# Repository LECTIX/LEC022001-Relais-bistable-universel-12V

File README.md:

# LEC022001 - Relais bistable universel 12V
Fichiers sources pour le produit LEC022001

## Description du produit

Ce module est un relais bistable disposant de toutes les protections nécessaires pour être utilisé avec une tension de 12 à 16 V alternative ou continue.
Comme tous les relais bistable, une seule impulsion est nécessaire pour faire basculer les contacts inverseurs d'un côté ou de l'autre, ce qui le rend idéal pour être utilisé avec des ILS ou bien des boutons poussoirs.
- **ALIMENTATION** 12 – 16 V AC / DC.
- **2 CONTACTS INVERSEURS** indépendants (DPDT).
- **FAIBLE CONSOMMATION** de 15 mA lorsqu'une des bobines relais est alimentée.
- **POUVOIR DE COUPURE** de 2A.

## Applications

- Cantonnement analogique
- Zone de protection faller car system
- Boucle de retournement
- Extension de contact inverseurs (aiguillages, relais, interrupteurs, …)
- Gestion d'un passage à niveau

## Installation

L’installation est simple et rapide :

1. Brancher le commun au pole négatif de l'alimentation.
1. Pour chacune des bornes R et S, intercaller un interrupteur ou équivalent (ILS, pédale, capteur Hall, contact inverseur, …) entre la borne et le pole positif de l'alimentation.
1. Les contacts inverseurs du relais réagissent en fonction du bouton sur lequel on appui.

**Attention** : Il ne faut en aucun cas alimenter les 2 bornes R et S simultanément.

## Utiliser les fichiers sources pour fabriquer le produit

Il n'est **pas nécessaire de savoir souder ou d'être bon en électronique** pour se procurer ce produit. Grâce aux fichiers sources publiés ici, vous pouvez être en mesure de faire fabriquer ce produit par un sous traitant.

### Faire fabriquer chez un sous traitant

Il est aujourd'hui possible de faire fabriquer à moindre cout des cartes électroniques. Nous recommendons [JLCPCB](https://jlcpcb.com/) si vous voulez aller au moins cher. Si vous préférez un acteur européen, [eurocircuits](https://www.eurocircuits.com/) est un des acteurs reconnus.

1. Télécherger les sources de ce produit en cliquant sur le bouton `Code`, puis `Download ZIP`.
1. Décompresser le dossier.
1. Les fichiers pour la fabrication se trouvent dans le répertoire `hardware/prod`.
1. Se connecter sur [https://cart.jlcpcb.com/quote](https://cart.jlcpcb.com/quote)
1. Cliquer sur le bouton `Add gerber file` et sélectionner le fichier `gerbers.zip`.
1. Sélectionnez la quantité de cartes que vous souhaitez dans le champs `PCB Qty`.
1. Laisser toutes les autres options par défaut, puis cliquez sur le toggle switch en face de `PCB Assembly`, et enfin sur le bouton `confirm`.
1. Une preview de la carte électronique sans les composants doit apparaitre. Cliquez sur `NEXT`.
1. Cliquez sur le bouton `Add BOM File`, puis sélectionnez le fichier `bom.csv`
1. Cliquez sur le bouton `Add CPL File`, puis sélectionnez le fichier `pos.csv`
1. **Vérifier que tous les composants sont en stock** et bien sélectionnés, puis cliquez sur `NEXT`.
1. Une preview de la carte avec ses composants apparait. Continuer le chemin en cliquant sur `NEXT`.
1. Le prix final apparait. Sélectionnez la catégorie du produit, puis cliquez sur `SAVE TO CART`.
1. Une fois sauvegardé dans votre panier, vous pouvez valider votre commande et choisir le moyen d'acheminement. Afin de ne pas avoir à se préoccuper des frais de douane, nous vous conseillons de choisir une méthode d'expédition DDP.

Vous receverez vos cartes sous 1 à 3 semaines. 

**Nous ne sommes en aucun cas responsables des cartes qui arriveraient défectueuses ou non fonctionnelles.**

### Modifications des fichiers sources

Installez kicad 6 (ou version supérieure), et ouvrez le fichier LEC022001.kicad_pro

### Regénérer les fichiers gerber, BOM, et position (Optionnel)

Peut se faire simplement en utilisant kikit :

```
cd hardware

# generate assembly files
docker run --rm -w /kikit -v $PWD:/kikit yaqwsx/kikit kikit fab jlcpcb --assembly --no-drc --schematic LEC022001.kicad_sch --field LCSC --corrections JLCPCB_CORRECTION --nametemplate LEC022001_{} LEC022001.kicad_pcb prod/

```

## License
Tous nos fichiers sont plubliés sous la license CERN Open Hardware Licence Version 2 - Strongly Reciprocal

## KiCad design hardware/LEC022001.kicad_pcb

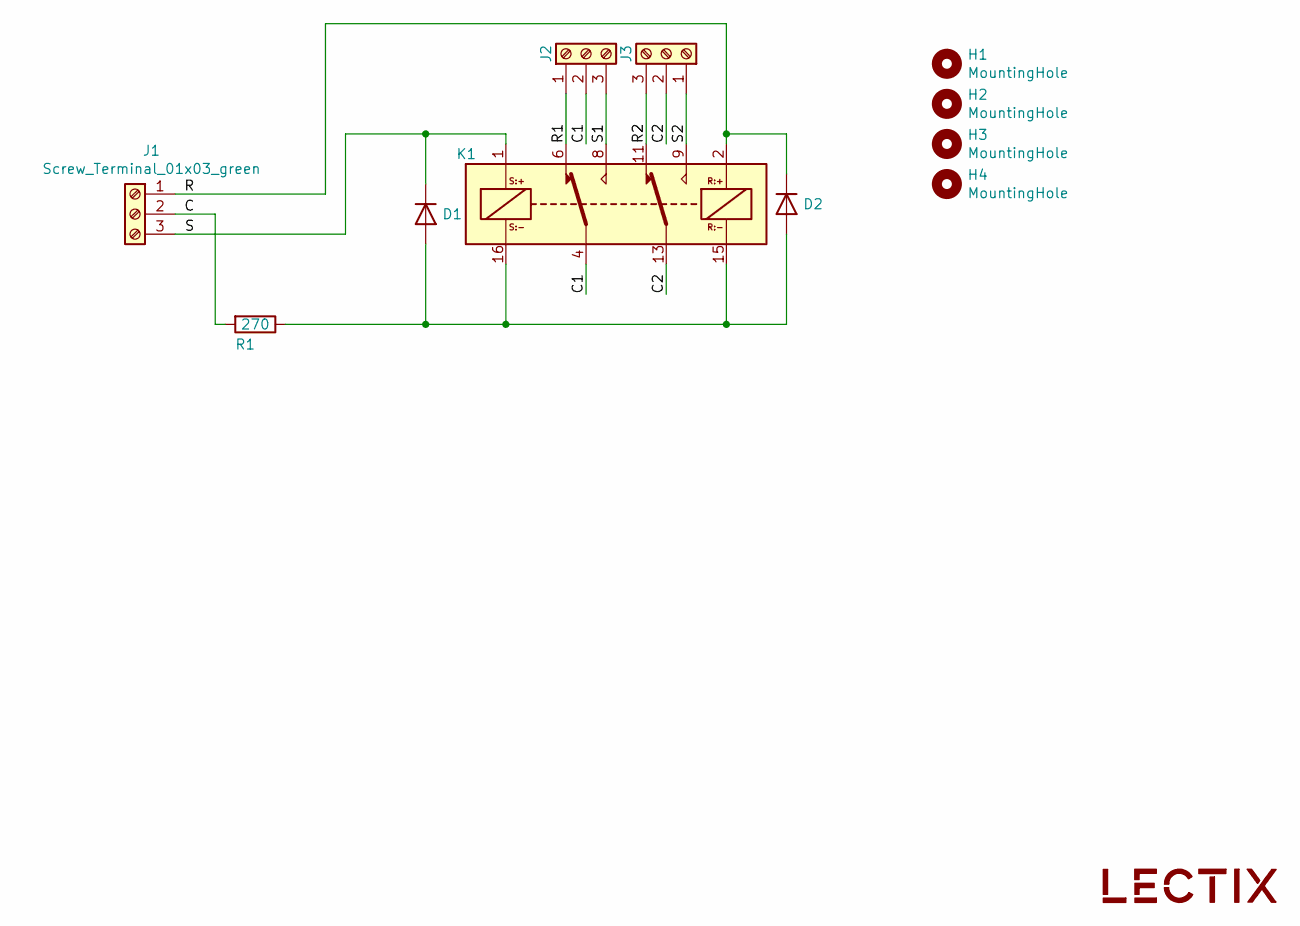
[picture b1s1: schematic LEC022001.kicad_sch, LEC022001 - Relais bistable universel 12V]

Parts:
D1, D2: 1N4148W; D_SOD-123; LCSC C81598
H1, H2, H3, H4: MountingHole; MountingHole_3.2mm_M3; JLCPCB BOM 0
J1: Screw_Terminal_01x03_green; TerminalBlock_bornier-3_P5.08mm-green; MPN DB126V-5.0-3P-GN; LCSC C395850
J2, J3: Screw_Terminal_01x03_blue; TerminalBlock_bornier-3_P5.08mm-blue; MPN DB301V-5.0-3P-BU-S; LCSC C395881
K1: HFD2-012-M-L2; Relay_DPDT_HFD2-xxx-M-L2; LCSC C399484
LOGO1: logo_lectix_25mm; Logo_10mm; JLCPCB BOM 0
R1: 270; R_0805_2012Metric; LCSC C17590

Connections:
/C: J1.2, R1.2
/C1: J2.2, K1.4
/C2: J3.2, K1.13
/R: D2.1 (K), J1.1, K1.2
/R1: J2.1, K1.6
/R2: J3.3, K1.11
/S: D1.1 (K), J1.3, K1.1
/S1: J2.3, K1.8
/S2: J3.1, K1.9
unnamed: D1.2 (A), D2.2 (A), K1.15, K1.16, R1.1

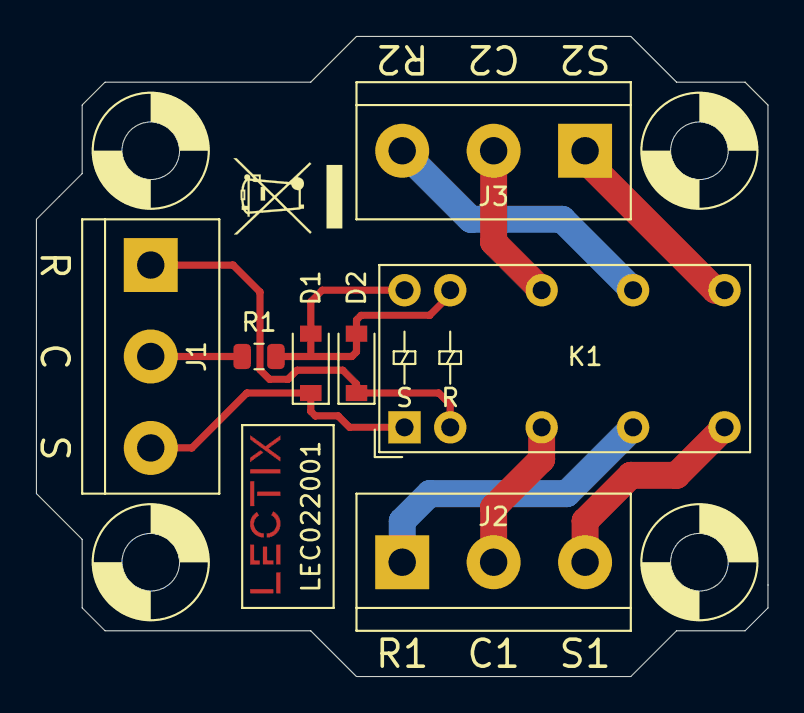
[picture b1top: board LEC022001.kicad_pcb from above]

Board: 2 copper layers, 40.6 x 35.6 mm, 12 parts (0 on the bottom side), 10 nets.

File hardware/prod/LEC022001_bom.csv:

Comment,Designator,Footprint,LCSC
1N4148W,"D1,D2",Diode_SMD:D_SOD-123,C81598
Screw_Terminal_01x03_green,J1,0_connectors:TerminalBlock_bornier-3_P5.08mm-green,C395850
Screw_Terminal_01x03_blue,"J2,J3",0_connectors:TerminalBlock_bornier-3_P5.08mm-blue,C395881
HFD2-012-M-L2,K1,0_relays:Relay_DPDT_HFD2-xxx-M-L2,C399484
270,R1,Resistor_SMD:R_0805_2012Metric,C17590

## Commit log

2023-04-19 Add hardware source files
